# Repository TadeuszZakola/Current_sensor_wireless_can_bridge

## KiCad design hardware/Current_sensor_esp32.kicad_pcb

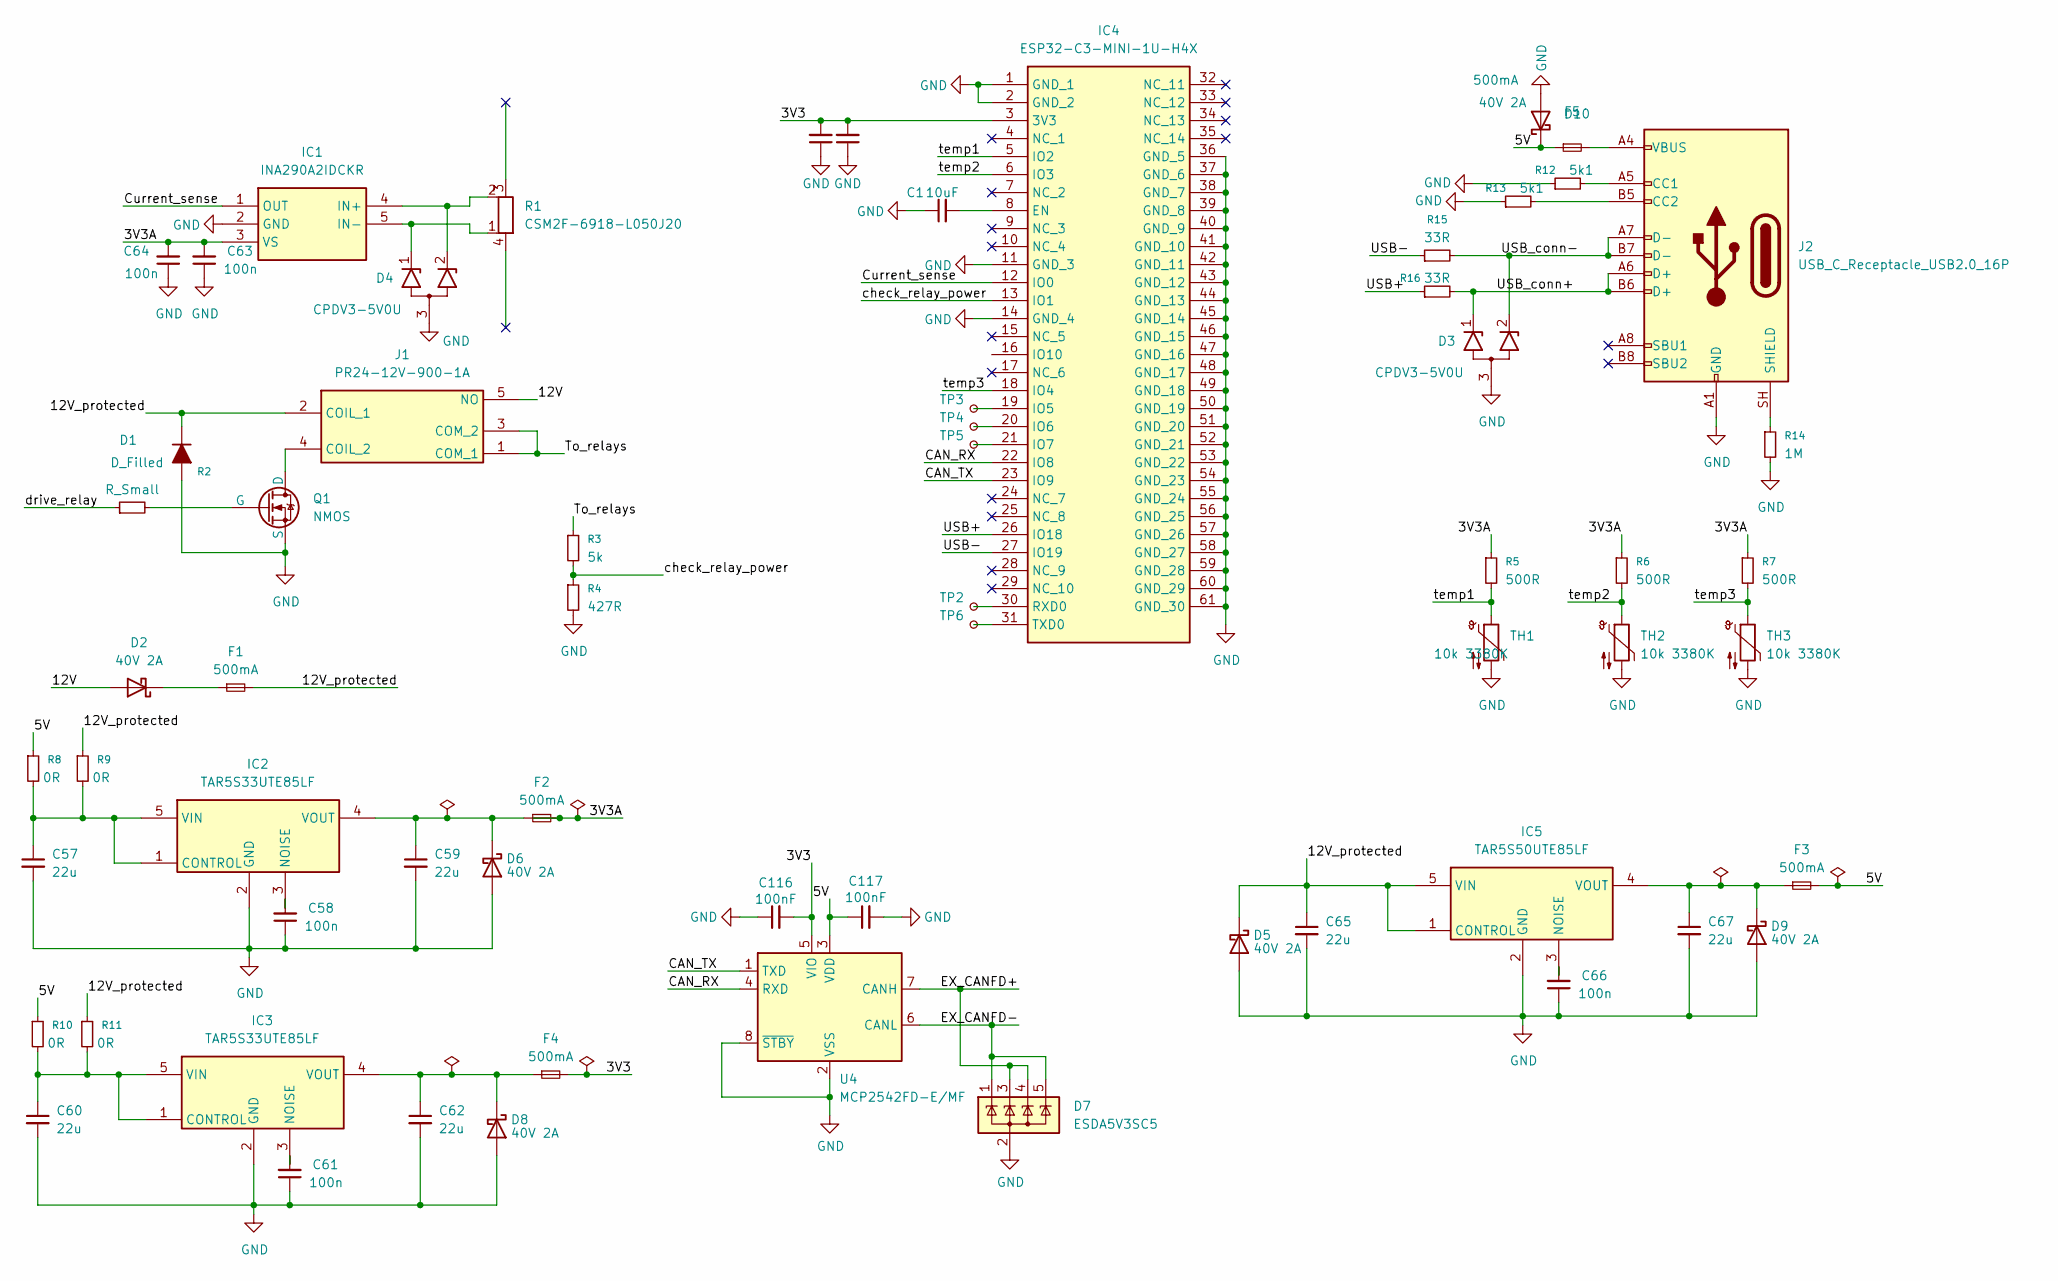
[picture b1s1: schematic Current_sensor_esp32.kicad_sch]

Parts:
C1: 10uF
C57, C59, C60, C62, C65, C67: 22u; C_0805_2012Metric_Pad1.18x1.45mm_HandSolder
C58, C61, C63, C64, C66, C68, C69: 100n; C_0603_1608Metric; Manufacturer_Part_Number C0603C104J3RACTU; Mouser Part Number 80-C0603C104J3R
C116, C117: 100nF; C_0603_1608Metric_Pad1.08x0.95mm_HandSolder; Manufacturer_Part_Number --; Mouser Part Number --
D1: D_Filled
D2, D5, D6, D8, D9, D10: 40V 2A; D_SOD-123F
D3, D4: CPDV3-5V0U; SOT-323_SC-70
D7: ESDA5V3SC5; SOT-23-5
F1, F2, F3, F4, F5: 500mA; R_0805_2012Metric_Pad1.20x1.40mm_HandSolder
IC1: INA290A2IDCKR; SOT65P210X110-5N; Mouser Part Number 595-INA290A2IDCKR
IC2, IC3: TAR5S33UTE85LF; SOTFL65P210X75-5N; Mouser Part Number 757-TAR5S33UTE85LF
IC4: ESP32-C3-MINI-1U-H4X; ESP32C3MINI1UH4X; Manufacturer_Part_Number ESP32-C3-MINI-1U-H4X
IC5: TAR5S50UTE85LF; SOTFL65P210X75-5N; Mouser Part Number 757-TAR5S33UTE85LF
J1: PR24-12V-900-1A; PR2412V9001A; Mouser Part Number 179-PR24-12V-900-1A
J2: USB_C_Receptacle_USB2.0_16P; USB_C_Receptacle_GCT_USB4085
Q1: NMOS
R1: CSM2F-6918-L050J20; CSM2F6918L050J20
R2: R_Small
R3: 5k; R_0603_1608Metric_Pad0.98x0.95mm_HandSolder
R4: 427R; R_0603_1608Metric_Pad0.98x0.95mm_HandSolder
R5, R6, R7: 500R; R_0603_1608Metric_Pad0.98x0.95mm_HandSolder
R8, R9, R10, R11: 0R; R_0603_1608Metric_Pad0.98x0.95mm_HandSolder
R12, R13: 5k1; R_0603_1608Metric_Pad0.98x0.95mm_HandSolder
R14: 1M; R_0603_1608Metric_Pad0.98x0.95mm_HandSolder
R15, R16: 33R; R_0603_1608Metric_Pad0.98x0.95mm_HandSolder
TH1, TH2, TH3: 10k 3380K; R_0603_1608Metric_Pad0.98x0.95mm_HandSolder
TP2, TP3, TP4, TP5, TP6: TestPoint_Small; TestPoint_Pad_1.0x1.0mm
U4: MCP2542FD-E/MF; DFN-8-1EP_3x3mm_P0.65mm_EP1.55x2.4mm; Manufacturer_Part_Number MCP2542FD-E/MF; Mouser Part Number 579-MCP2542FD-E/MF

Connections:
/3V3: C68.2, C69.2, C116.2, F4.2, IC4.3 (3V3), U4.5 (VIO)
/3V3A: C63.2, C64.2, F2.2, IC1.3 (VS), R5.1, R6.1, R7.1
/5V: C117.1, D10.1 (K), F3.2, F5.1, R8.1, R10.1, U4.3 (VDD)
/12V: D2.2 (A), J1.5 (NO)
/12V_protected: C65.1, D1.1 (K), D5.1 (K), F1.2, IC5.1 (CONTROL), IC5.5 (VIN), J1.2 (COIL_1), R9.1, R11.1
/CAN_RX: IC4.22 (IO8), U4.4 (RXD)
/CAN_TX: IC4.23 (IO9), U4.1 (TXD)
/Current_sense: IC1.1 (OUT), IC4.12 (IO0)
/EX_CANFD+: D7.3 (K), D7.4 (K), U4.7 (CANH)
/EX_CANFD-: D7.1 (K), D7.5 (K), U4.6 (CANL)
/To_relays: J1.1 (COM_1), J1.3 (COM_2), R3.1
/USB+: IC4.26 (IO18), R16.1
/USB-: IC4.27 (IO19), R15.1
/USB_conn+: D3.1 (K1), J2.A6 (D+), J2.B6 (D+), R16.2
/USB_conn-: D3.2 (K2), J2.A7 (D-), J2.B7 (D-), R15.2
/check_relay_power: IC4.13 (IO1), R3.2, R4.1
/temp1: IC4.5 (IO2), R5.2, TH1.1
/temp2: IC4.6 (IO3), R6.2, TH2.1
/temp3: IC4.18 (IO4), R7.2, TH3.1
GND: C1.1, C57.2, C58.1, C59.2, C60.2, C61.1, C62.2, C63.1, C64.1, C65.2, C66.1, C67.2, C68.1, C69.1, C116.1, C117.2, D1.2 (A), D3.3 (A), D4.3 (A), D5.2 (A), D6.2 (A), D7.2 (A), D8.2 (A), D9.2 (A), D10.2 (A), IC1.2 (GND), IC2.2 (GND), IC3.2 (GND), IC4.1 (GND_1), IC4.2 (GND_2), IC4.11 (GND_3), IC4.14 (GND_4), IC4.36 (GND_5), IC4.37 (GND_6), IC4.38 (GND_7), IC4.39 (GND_8), IC4.40 (GND_9), IC4.41 (GND_10), IC4.42 (GND_11), IC4.43 (GND_12), IC4.44 (GND_13), IC4.45 (GND_14), IC4.46 (GND_15), IC4.47 (GND_16), IC4.48 (GND_17), IC4.49 (GND_18), IC4.50 (GND_19), IC4.51 (GND_20), IC4.52 (GND_21), IC4.53 (GND_22), IC4.54 (GND_23), IC4.55 (GND_24), IC4.56 (GND_25), IC4.57 (GND_26), IC4.58 (GND_27), IC4.59 (GND_28), IC4.60 (GND_29), IC4.61 (GND_30), IC5.2 (GND), J2.A1 (GND), J2.A12 (GND), J2.B1 (GND), J2.B12 (GND), Q1.3 (S), R4.2, R12.1, R13.1, R14.2, TH1.2, TH2.2, TH3.2, U4.2 (VSS), U4.8 (~STBY), U4.9 (VSS)
unnamed: D2.1 (K), F1.1
unnamed: D4.1 (K1), IC1.5 (IN-), R1.1
unnamed: D4.2 (K2), IC1.4 (IN+), R1.2
unnamed: C59.1, D6.1 (K), F2.1, IC2.4 (VOUT)
unnamed: C62.1, D8.1 (K), F4.1, IC3.4 (VOUT)
unnamed: C67.1, D9.1 (K), F3.1, IC5.4 (VOUT)
unnamed: F5.2, J2.A4 (VBUS), J2.A9 (VBUS), J2.B4 (VBUS), J2.B9 (VBUS)
unnamed: C57.1, IC2.1 (CONTROL), IC2.5 (VIN), R8.2, R9.2
unnamed: C58.2, IC2.3 (NOISE)
unnamed: C60.1, IC3.1 (CONTROL), IC3.5 (VIN), R10.2, R11.2
unnamed: C61.2, IC3.3 (NOISE)
unnamed: C1.2, IC4.8 (EN)
unnamed: IC4.19 (IO5), TP3.1 (1_1)
unnamed: IC4.20 (IO6), TP4.1 (1_1)
unnamed: IC4.21 (IO7), TP5.1 (1_1)
unnamed: IC4.30 (RXD0), TP2.1 (1_1)
unnamed: IC4.31 (TXD0), TP6.1 (1_1)
unnamed: C66.2, IC5.3 (NOISE)
unnamed: J1.4 (COIL_2), Q1.1 (D)
unnamed: J2.A5 (CC1), R12.2
unnamed: J2.B5 (CC2), R13.2
unnamed: J2.SH (SHIELD), R14.1
unnamed: Q1.2 (G), R2.2

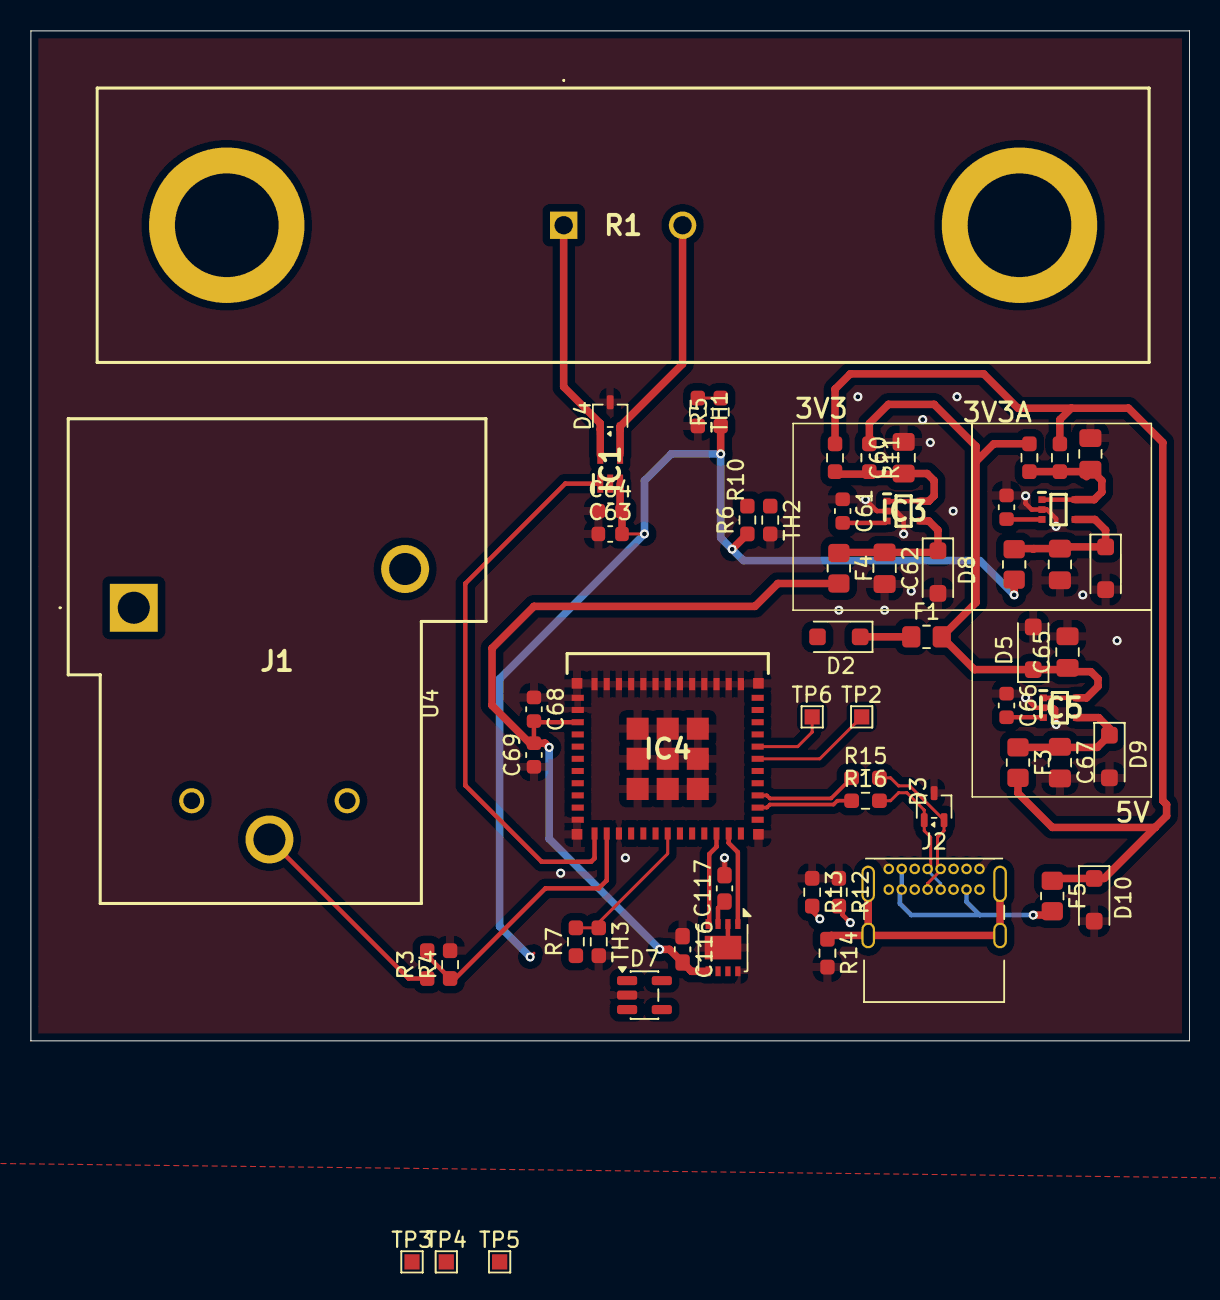
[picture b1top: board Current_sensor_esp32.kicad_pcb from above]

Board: 4 copper layers, 76.0 x 66.2 mm, 60 parts (0 on the bottom side), 40 nets.

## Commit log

2026-04-02 Dodano zabezpieczenia, sensing napiec oraz wstepny layout
